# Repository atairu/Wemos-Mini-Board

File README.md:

Wemos mini breakout board with mullti voltage for use with WLED

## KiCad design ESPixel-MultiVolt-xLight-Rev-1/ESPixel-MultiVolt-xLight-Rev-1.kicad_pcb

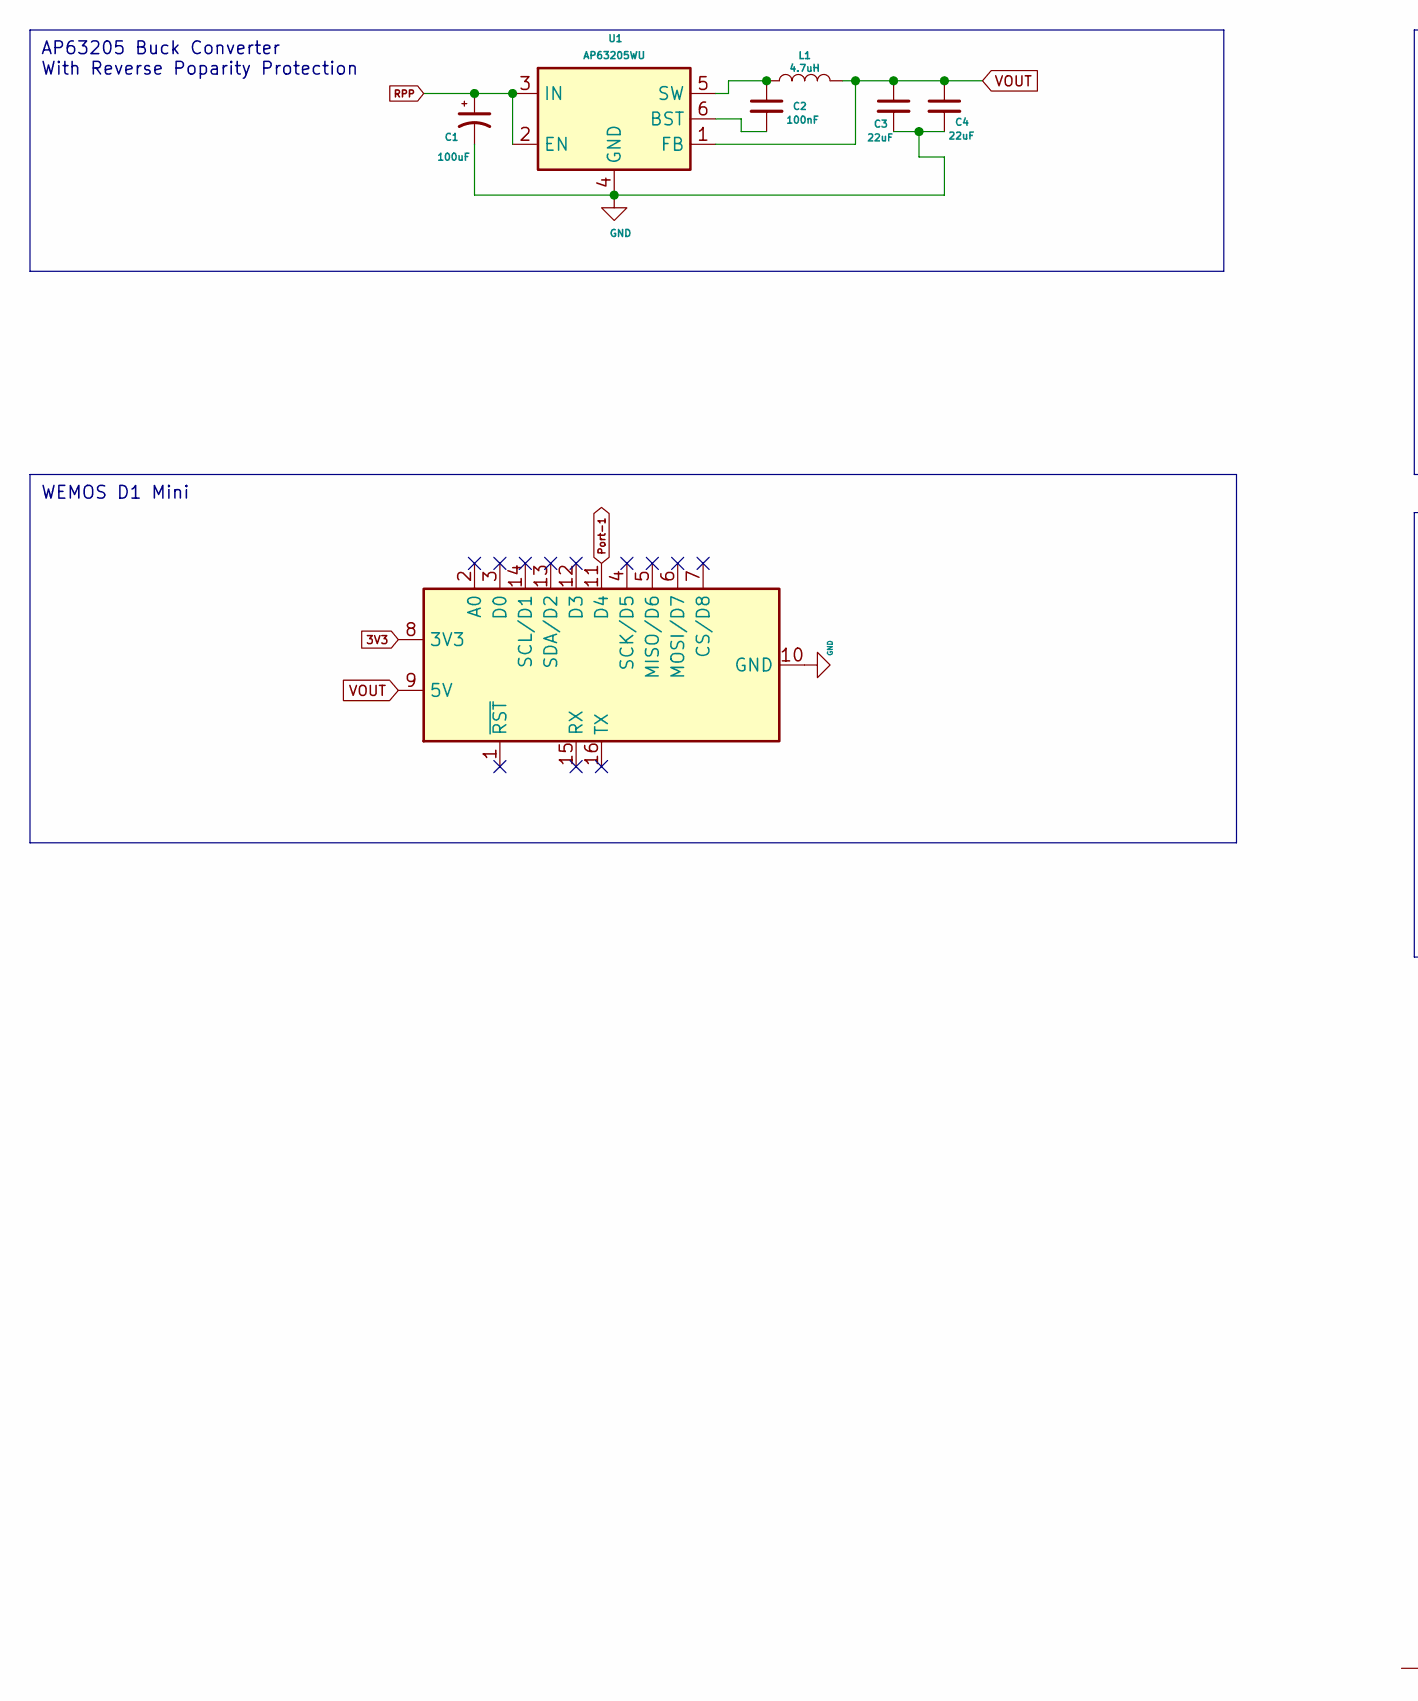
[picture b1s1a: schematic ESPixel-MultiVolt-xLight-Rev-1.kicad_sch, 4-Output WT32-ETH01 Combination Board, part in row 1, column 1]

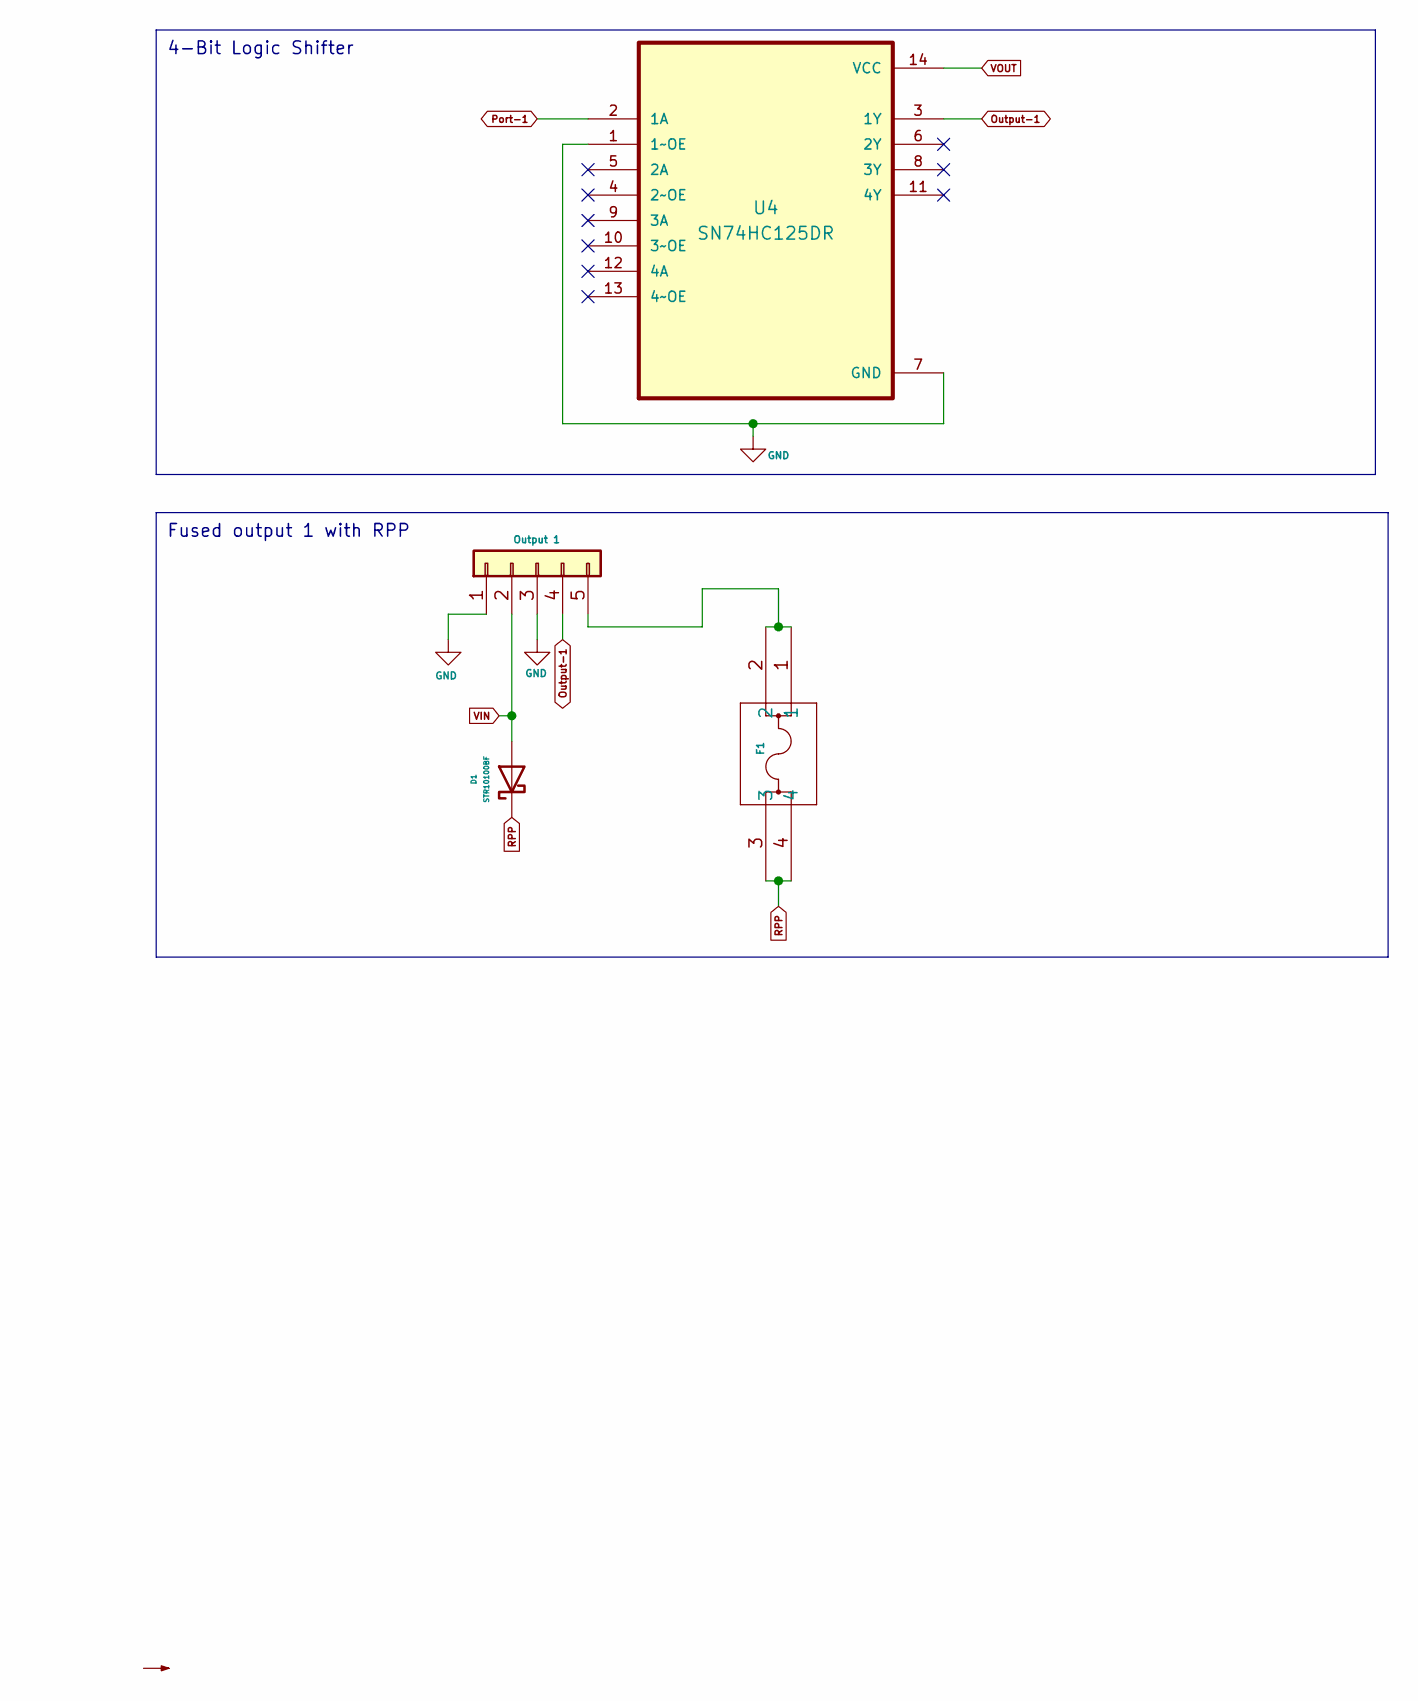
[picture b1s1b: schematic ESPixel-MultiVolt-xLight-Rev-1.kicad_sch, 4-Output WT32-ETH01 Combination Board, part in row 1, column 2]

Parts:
C1: 100uF; CP_Elec_6.3x5.4
C2: 100nF; C_0805_2012Metric_Pad1.18x1.45mm_HandSolder
C3, C4: 22uF; C_0805_2012Metric_Pad1.18x1.45mm_HandSolder
D1: STR10100BF; D_SMB_Handsoldering
F1: MCCQ-122_MTC
JST1: Output 1; TerminalBlock_Phoenix_MKDS-1,5-5-5.08_1x05_P5.08mm_Horizont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
L1: 4.7uH; L_Taiyo-Yuden_MD-5050
U1: AP63205WU; TSOT-23-6
U2: WeMos_D1_mini; WEMOS_D1_mini_light
U4: SN74HC125DR; SOIC127P600X175-14N

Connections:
3V3: U2.8 (3V3)
GND: C1.2, C3.2, C4.2, JST1.1, JST1.3, U1.4 (GND), U2.10 (GND), U4.1 (1~OE), U4.7 (GND)
unnamed: F1.1, F1.2, JST1.5
unnamed: C2.2, U1.6 (BST)
unnamed: C2.1, L1.1, U1.5 (SW)
Output-1: JST1.4, U4.3 (1Y)
Port-1: U2.11 (D4), U4.2 (1A)
RPP: C1.1, D1.1 (K), F1.3, F1.4, U1.2 (EN), U1.3 (IN)
VIN: D1.2 (A), JST1.2
VOUT: C3.1, C4.1, L1.2, U1.1 (FB), U2.9 (5V), U4.14 (VCC)

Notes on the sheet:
AP63205 Buck Converter With Reverse Poparity Protection
4-Bit Logic Shifter
WEMOS D1 Mini
Fused output 1 with RPP

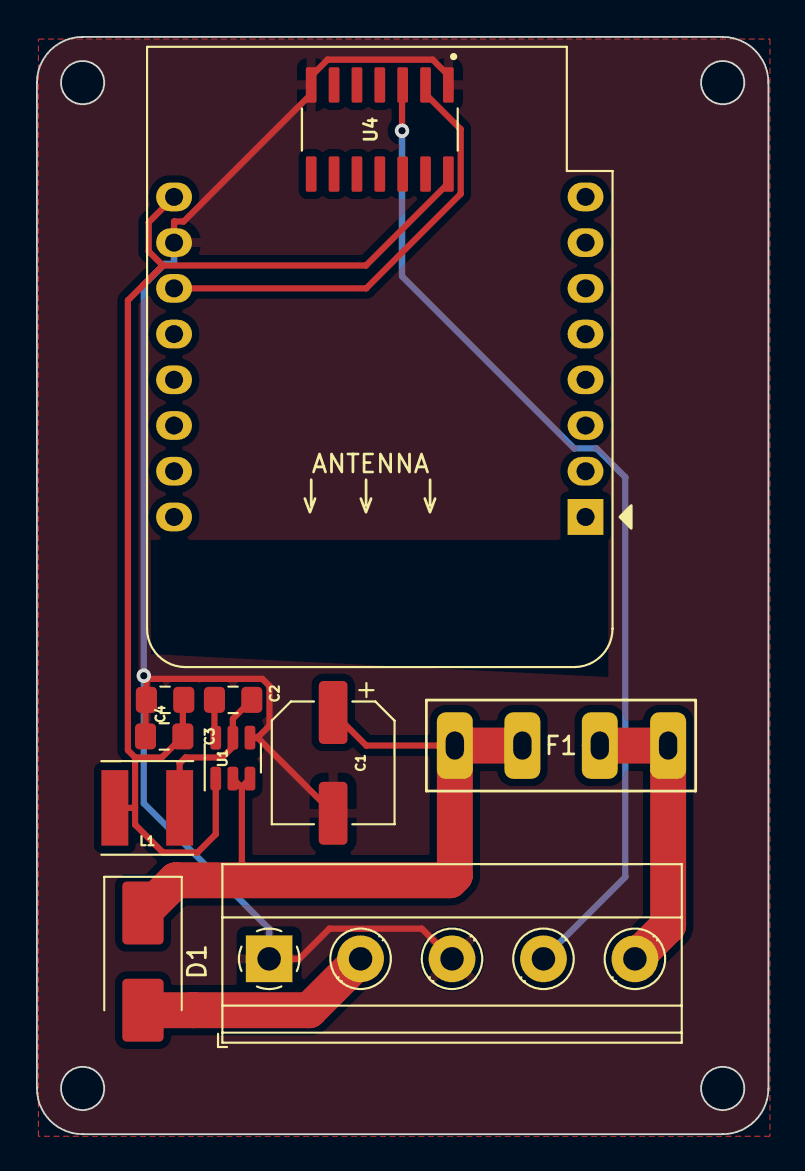
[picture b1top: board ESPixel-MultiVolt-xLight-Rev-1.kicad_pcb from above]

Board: 2 copper layers, 40.6 x 61.0 mm, 11 parts (0 on the bottom side), 9 nets.
